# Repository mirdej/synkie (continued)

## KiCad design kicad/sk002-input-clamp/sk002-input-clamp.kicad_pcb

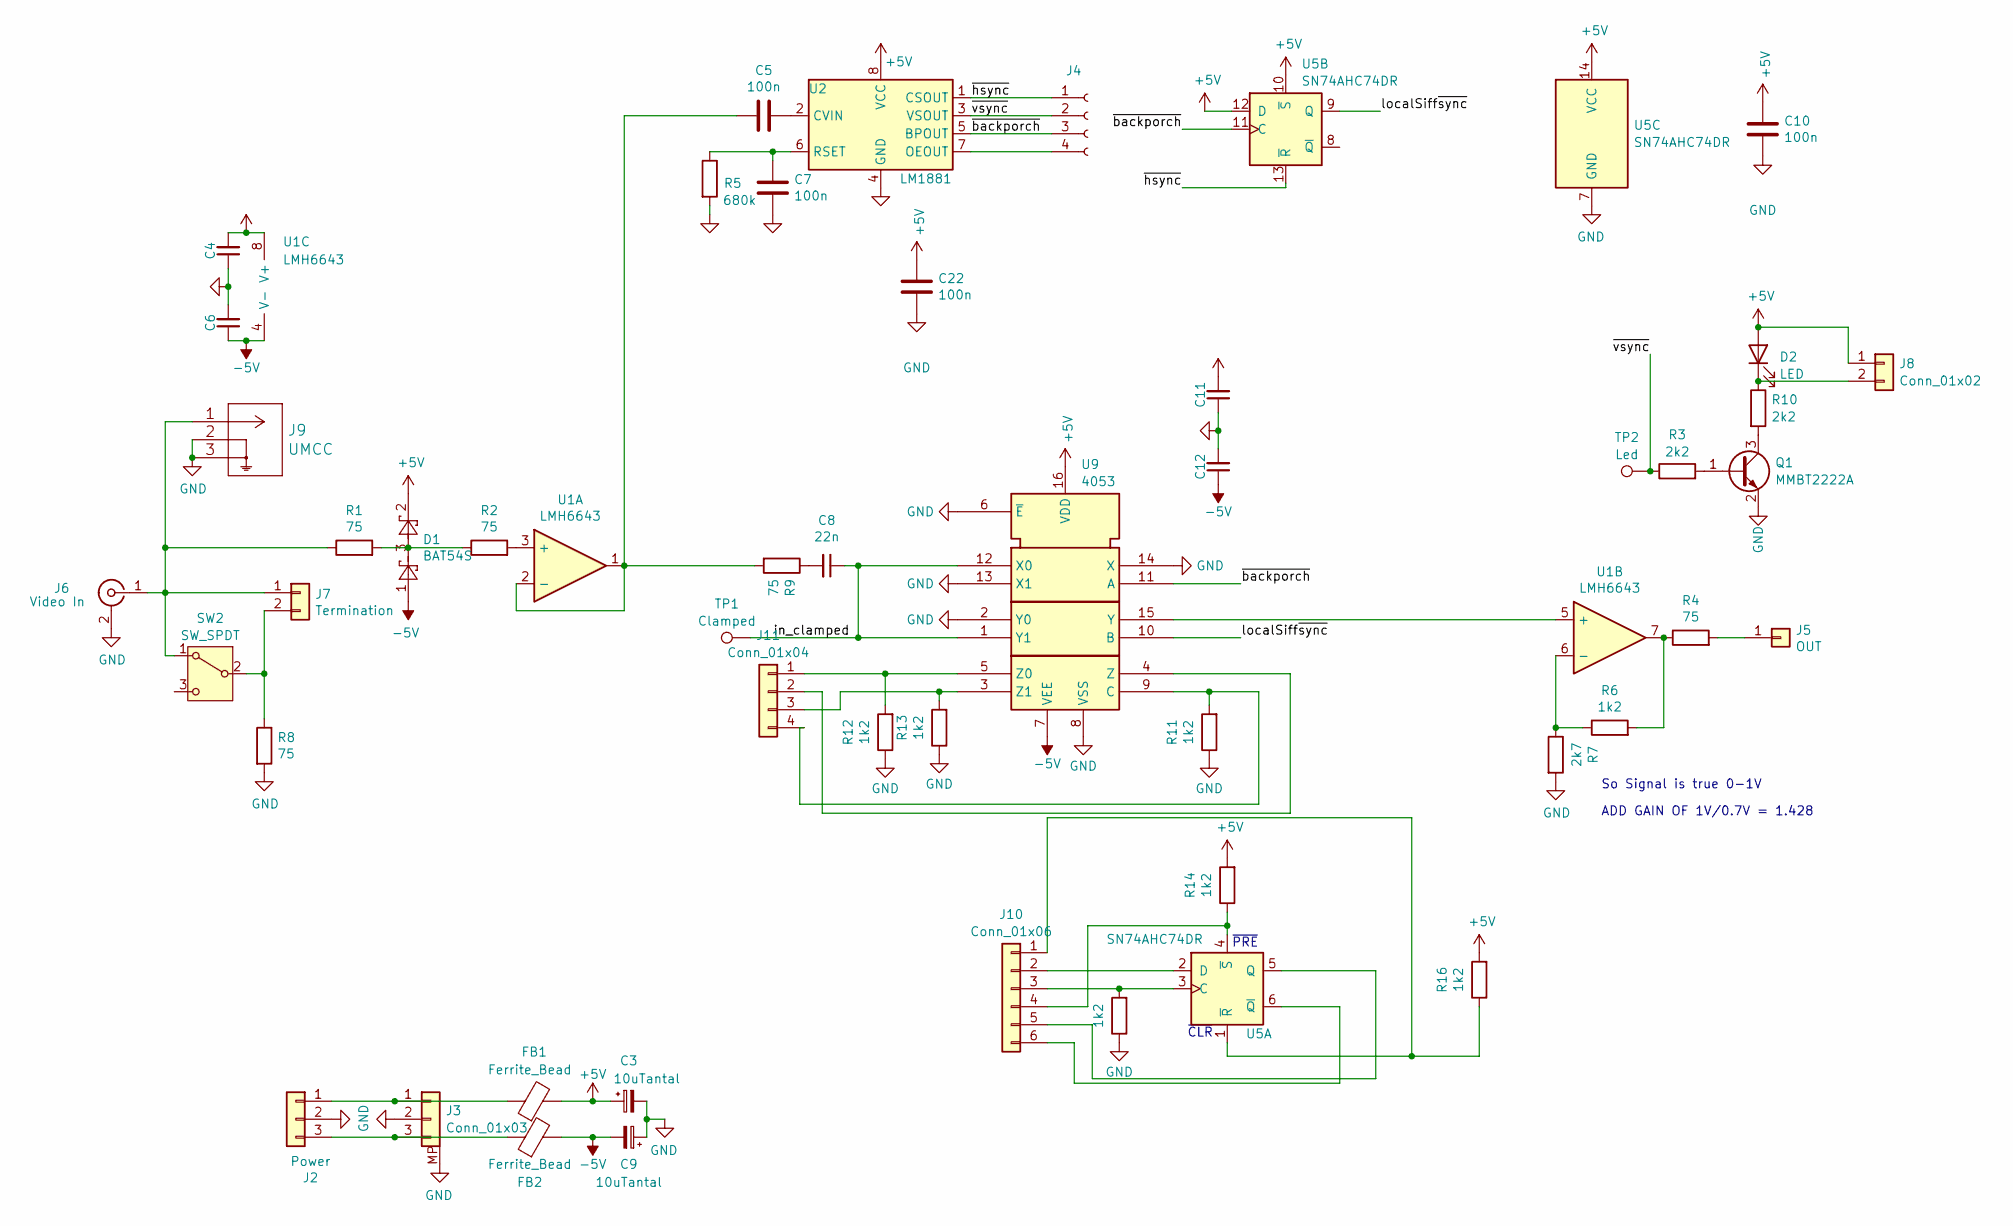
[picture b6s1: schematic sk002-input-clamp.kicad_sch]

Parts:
C3, C9: 10uTantal; CP_EIA-3216-18_Kemet-A; LCSC C7171
C4, C5, C6, C7, C10, C11, C12, C22: 100n; C_0603_1608Metric; LCSC C14663
C8: 22n; C_0603_1608Metric; LCSC C21122
D1: BAT54S; SOT-23; LCSC C7420333
D2: LED; LED_0805_2012Metric; LCSC C2296
FB1, FB2: Ferrite_Bead; L_0805_2012Metric; LCSC C1017
J2: Power; Molex_KK-254_AE-6410-03A_1x03_P2.54mm_Vertical
J3: Conn_01x03; Hirose_DF13-03P-1.25DSA_1x03_P1.25mm_Vertical; LCSC C293633
J4: Conn_01x04_Socket; PinHeader_1x04_P2.54mm_Vertical
J5: OUT; TestPoint_THTPad_D4.0mm_Drill2.0mm
J6: Video In; BNC_Aliexpress
J7: Termination; PinHeader_1x02_P2.54mm_Vertical
J8: Conn_01x02; PinHeader_1x02_P2.54mm_Vertical
J9: UMCC; TE_UMCC_2337019-1; LCSC C5137195
J10: Conn_01x06; PinHeader_1x06_P2.54mm_Vertical
J11: Conn_01x04; PinHeader_1x04_P2.54mm_Vertical
Q1: MMBT2222A; SOT-23; LCSC C8512
R1, R2, R4, R8, R9: 75; R_0603_1608Metric; LCSC C4275
R3, R10: 2k2; R_0603_1608Metric; LCSC C4190
R5: 680k; R_0603_1608Metric; LCSC C25822
R6, R11, R12, R13, R14, R15, R16: 1k2; R_0603_1608Metric; LCSC C22765
R7: 2k7; R_0603_1608Metric; LCSC C13167
SW2: SW_SPDT; CUS-12TB_NDC; LCSC C109335
TP1: Clamped; TestPoint_Pad_2.0x2.0mm
TP2: Led; TestPoint_Pad_D1.0mm
U1: LMH6643; VSSOP-8_3x3mm_P0.65mm; LCSC C478382
U2: LM1881; SOIC-8_3.9x4.9mm_P1.27mm; LCSC C518922
U5: SN74AHC74DR; SOIC-14_3.9x8.7mm_P1.27mm; LCSC C7621
U9: 4053; SOIC-16_3.9x9.9mm_P1.27mm; LCSC C7500846

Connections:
+5V: C3.1, C4.2, C10.1, C11.2, C22.1, D1.2, D2.2 (A), FB1.2, J8.1, R14.2, R16.2, U1.8 (V+), U2.8 (VCC), U5.10 (~S), U5.12 (D), U5.14 (VCC), U9.16 (VDD)
-5V: C6.1, C9.2, C12.1, D1.1, FB2.2, U1.4 (V-), U9.7 (VEE)
/in_clamped: C8.1, TP1.1 (1_1), U9.1 (Y1), U9.12 (X0)
/localSiff~sync: U5.9 (Q), U9.10 (B)
/~backporch: J4.3, U2.5 (BPOUT), U5.11 (C), U9.11 (A)
/~hsync: J4.1, U2.1 (CSOUT), U5.13 (~R)
/~vsync: J4.2, R3.1, TP2.1 (1_1), U2.3 (VSOUT)
GND: C3.2, C4.1, C6.2, C7.2, C9.1, C10.2, C11.1, C12.2, C22.2, J2.2, J3.2, J3.MP, J6.2 (Ext), J9.2, J9.3, Q1.2 (E), R5.2, R7.2, R8.2, R11.1, R12.1, R13.1, R15.1, U2.4 (GND), U5.7 (GND), U9.2 (Y0), U9.6 (~E), U9.8 (VSS), U9.13 (X1), U9.14 (X)
unnamed: C8.2, R9.1
unnamed: D1.3, R1.2, R2.1
unnamed: D2.1 (K), J8.2, R10.1
unnamed: FB1.1, J2.1, J3.1
unnamed: FB2.1, J2.3, J3.3
unnamed: J4.4, U2.7 (OEOUT)
unnamed: J5.1 (Pin_1_1), R4.2
unnamed: J6.1 (In), J7.1, J9.1, R1.1, SW2.1 (A)
unnamed: J7.2, R8.1, SW2.2 (B)
unnamed: J10.1, R16.1, U5.1 (~R)
unnamed: J10.2, U5.2 (D)
unnamed: J10.3, R15.2, U5.3 (C)
unnamed: J10.4, R14.1, U5.4 (~S)
unnamed: J10.5, U5.5 (Q)
unnamed: J10.6, U5.6 (~Q)
unnamed: J11.1, R12.2, U9.5 (Z0)
unnamed: J11.2, U9.4 (Z)
unnamed: J11.3, R13.2, U9.3 (Z1)
unnamed: J11.4, R11.2, U9.9 (C)
unnamed: Q1.1 (B), R3.2
unnamed: Q1.3 (C), R10.2
unnamed: R4.1, R6.2, U1.7
unnamed: R2.2, U1.3 (+)
unnamed: C5.2, R9.2, U1.1, U1.2 (-)
unnamed: U1.5 (+), U9.15 (Y)
unnamed: R6.1, R7.1, U1.6 (-)
unnamed: C5.1, U2.2 (CVIN)
unnamed: C7.1, R5.1, U2.6 (RSET)

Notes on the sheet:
~{CLR}
ADD GAIN OF 1V/0.7V = 1.428
~{PRE}
So Signal is true 0-1V

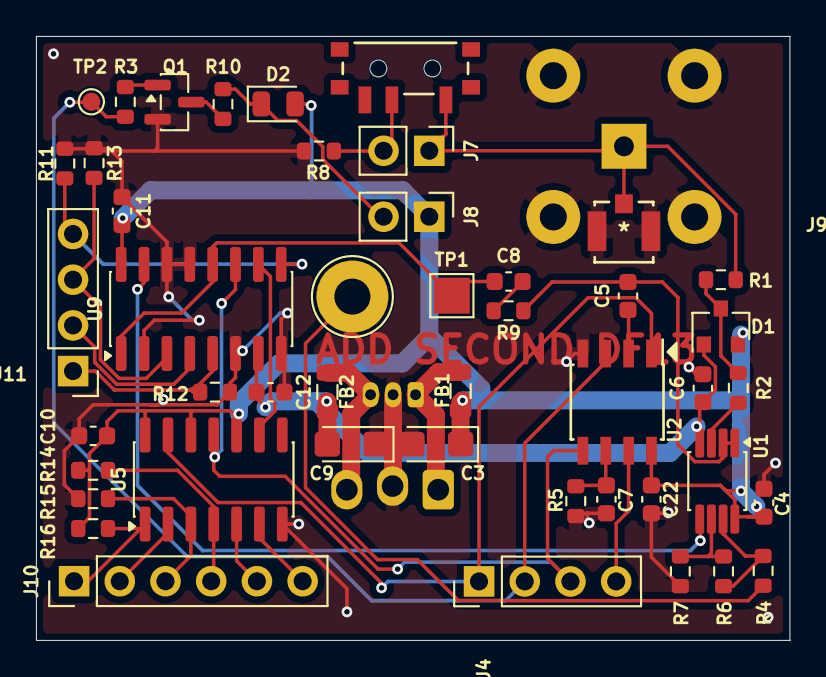
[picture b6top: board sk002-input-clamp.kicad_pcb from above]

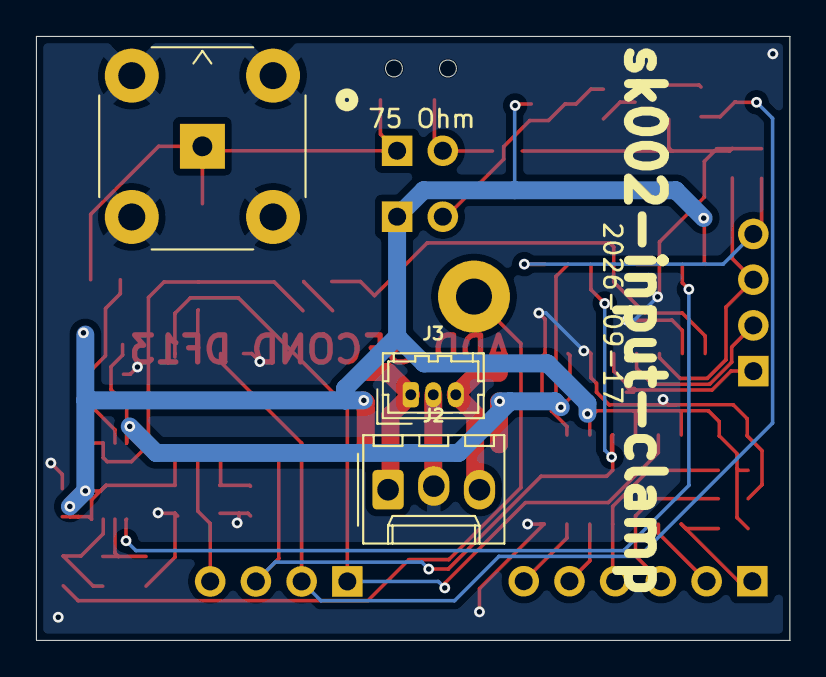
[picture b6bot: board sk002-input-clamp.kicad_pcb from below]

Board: 2 copper layers, 41.9 x 33.6 mm, 49 parts (3 on the bottom side), 36 nets.

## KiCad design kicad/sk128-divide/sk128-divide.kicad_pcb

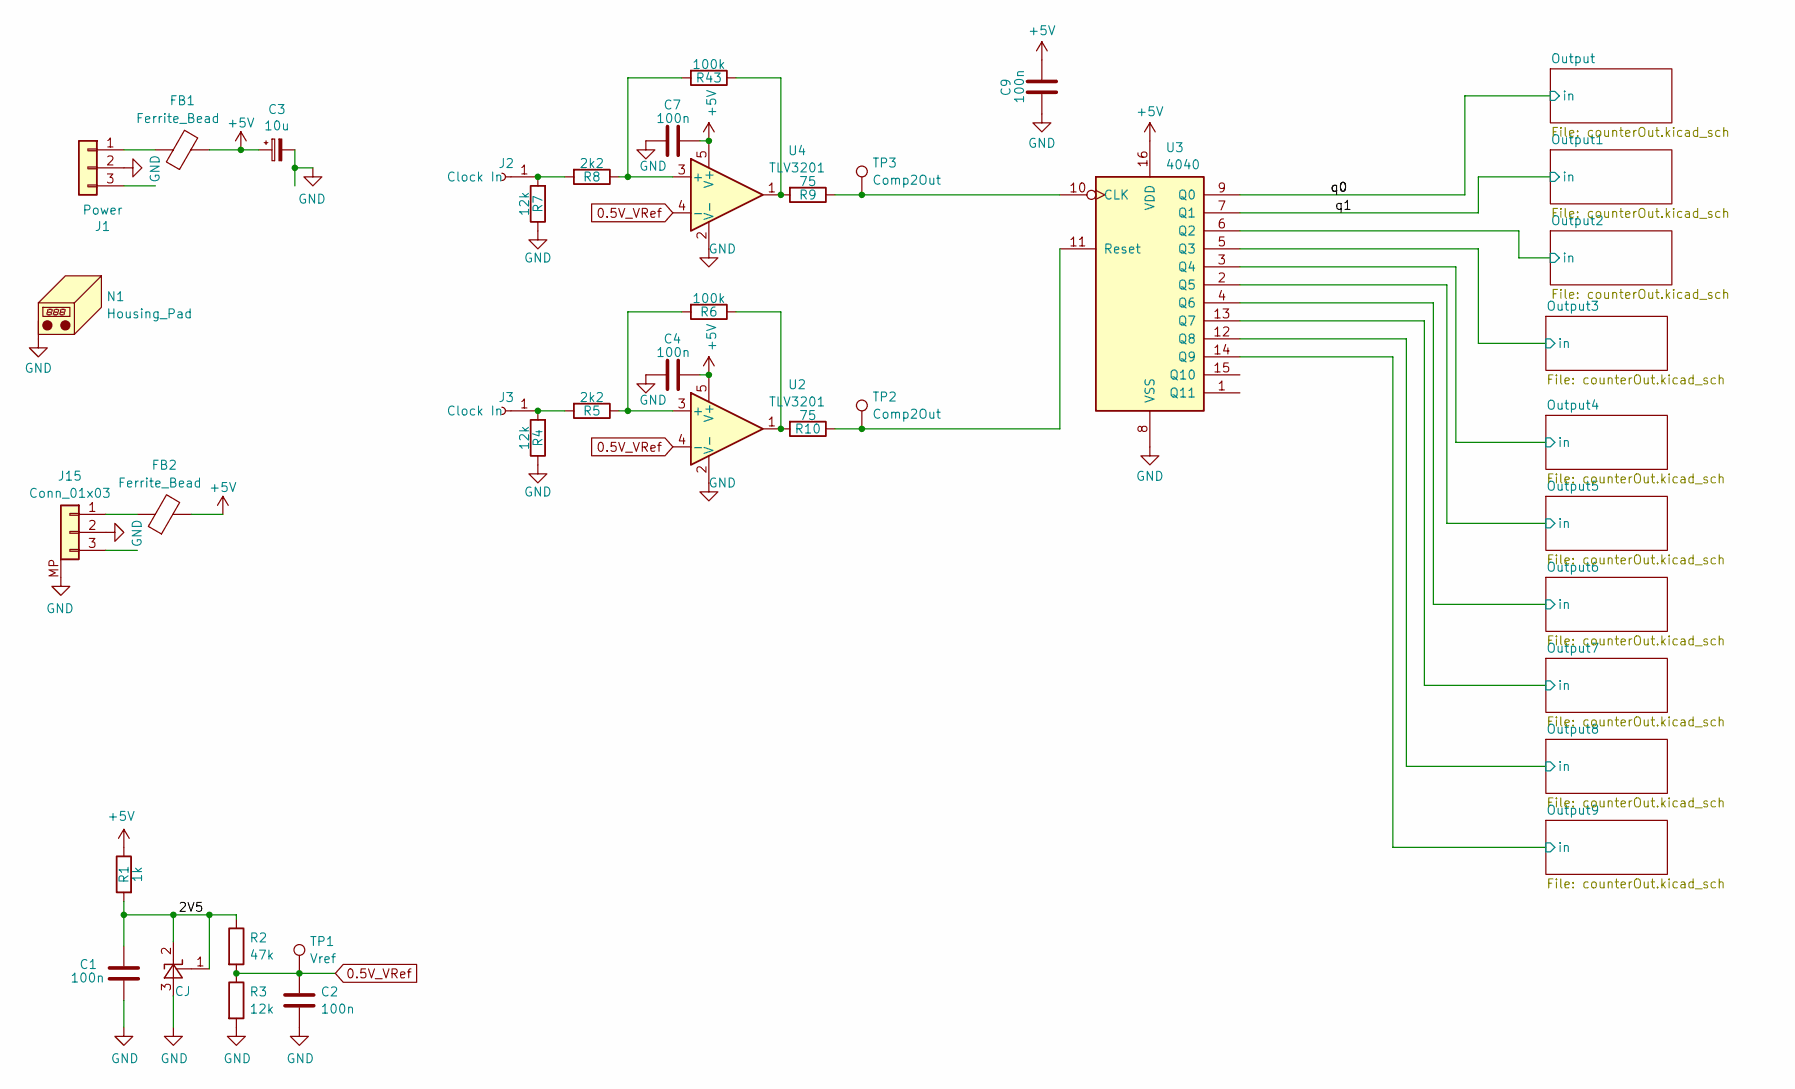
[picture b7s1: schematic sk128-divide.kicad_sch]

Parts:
C1, C2, C4, C7, C9: 100n; C_0603_1608Metric; LCSC C14663
C3: 10u; C_0805_2012Metric; LCSC C15850
FB1, FB2: Ferrite_Bead; L_0805_2012Metric; LCSC C1017
J1: Power; Molex_KK-254_AE-6410-03A_1x03_P2.54mm_Vertical_SMD
J2, J3: Clock In; Banana2mm-Löthülse
J15: Conn_01x03; Molex_PicoBlade_53398-0371_1x03-1MP_P1.25mm_Vertical; LCSC C293633
N1: Housing_Pad; Frontplate_20mm
R1: 1k; R_0603_1608Metric; LCSC C21190
R2: 47k; R_0603_1608Metric; LCSC C25819
R3, R4, R7: 12k; R_0603_1608Metric; LCSC C22790
R5, R8: 2k2; R_0603_1608Metric; LCSC C4190
R6, R43: 100k; R_0603_1608Metric; LCSC C25803
R9, R10: 75; R_0603_1608Metric; LCSC C4275
TP1: Vref; TestPoint_Pad_D1.0mm
TP2, TP3: Comp2Out; TestPoint_Pad_D1.0mm
U1: CJ; SOT-23; LCSC C3113
U2, U4: TLV3201; SOT-23-5; LCSC C105188
U3: 4040; SOIC-16_3.9x9.9mm_P1.27mm; LCSC C22390247

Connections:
0.5V_VRef: C2.1, R2.2, R3.1, TP1.1 (1_1), U2.4 (-), U4.4 (-)
+5V: C3.1, C4.2, C7.2, C9.2, FB1.2, FB2.2, R1.1, U2.5 (V+), U3.16 (VDD), U4.5 (V+); also elsewhere on the board
/2V5: C1.1, R1.2, R2.1, U1.1 (R), U1.2 (K)
/Output2/in: U3.6 (Q2); also elsewhere on the board
/Output3/in: U3.5 (Q3); also elsewhere on the board
/Output4/in: U3.3 (Q4); also elsewhere on the board
/Output5/in: U3.2 (Q5); also elsewhere on the board
/Output6/in: U3.4 (Q6); also elsewhere on the board
/Output7/in: U3.13 (Q7); also elsewhere on the board
/Output8/in: U3.12 (Q8); also elsewhere on the board
/Output9/in: U3.14 (Q9); also elsewhere on the board
/Output/in: U3.9 (Q0); also elsewhere on the board
/q1: U3.7 (Q1); also elsewhere on the board
GND: C1.2, C2.2, C3.2, C4.1, C7.1, C9.1, J1.2, J15.2, J15.MP, N1.1 (PAD_1), R3.2, R4.1, R7.1, U1.3 (A), U2.2 (V-), U3.8 (VSS), U4.2 (V-); also elsewhere on the board
unnamed: FB1.1, J1.1
unnamed: J2.1 (Pin_1_1), R7.2, R8.2
unnamed: J3.1 (Pin_1_1), R4.2, R5.2
unnamed: FB2.1, J15.1
unnamed: R6.1, R10.2, U2.1
unnamed: R9.2, R43.1, U4.1
unnamed: R5.1, R6.2, U2.3 (+)
unnamed: R9.1, TP3.1 (1_1), U3.10 (CLK)
unnamed: R10.1, TP2.1 (1_1), U3.11 (Reset)
unnamed: R8.1, R43.2, U4.3 (+)

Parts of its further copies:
R18: 2k2; R_0603_1608Metric; LCSC C4190

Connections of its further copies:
unnamed 15: R18.1; also elsewhere on the board
unnamed 41: R18.2; also elsewhere on the board

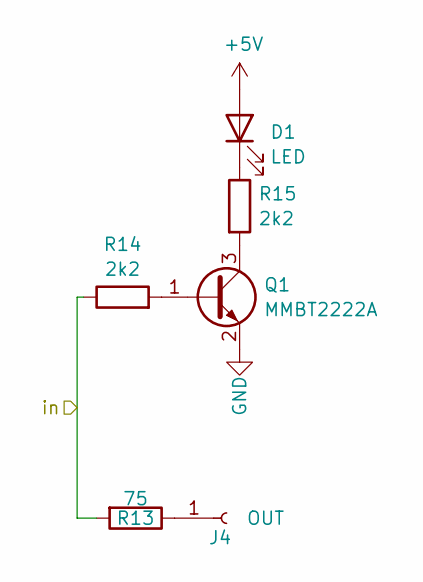
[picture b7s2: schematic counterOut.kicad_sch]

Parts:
D1: LED; LED_1206_3216Metric_ReverseMount_Hole1.8x2.4mm; LCSC C125108
J4: OUT; Banana2mm-Löthülse
Q1: MMBT2222A; SOT-23; LCSC C8512
R13: 75; R_0603_1608Metric; LCSC C4275
R14, R15: 2k2; R_0603_1608Metric; LCSC C4190

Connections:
+5V: D1.2 (A); also elsewhere on the board
/Output/in: R13.2, R14.1; also elsewhere on the board
GND: Q1.2 (E); also elsewhere on the board
unnamed: D1.1 (K), R15.1
unnamed: J4.1 (Pin_1_1), R13.1
unnamed: Q1.1 (B), R14.2
unnamed: Q1.3 (C), R15.2

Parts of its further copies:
D2, D3, D4, D5, D6, D7, D8, D9, D10: LED; LED_1206_3216Metric_ReverseMount_Hole1.8x2.4mm; LCSC C125108
J5, J6, J7, J8, J9, J10, J11, J12, J13: OUT; Banana2mm-Löthülse
Q2, Q3, Q4, Q5, Q6, Q7, Q8, Q9, Q10: MMBT2222A; SOT-23; LCSC C8512
R16, R18, R19, R21, R22, R24, R25, R27, R28, R30, R31, R33, R34, R36, R37, R39, R40, R42: 2k2; R_0603_1608Metric; LCSC C4190
R17, R20, R23, R26, R29, R32, R35, R38, R41: 75; R_0603_1608Metric; LCSC C4275

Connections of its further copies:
+5V: D2.2 (A), D3.2 (A), D4.2 (A), D5.2 (A), D6.2 (A), D7.2 (A), D8.2 (A), D9.2 (A), D10.2 (A); also elsewhere on the board
/Output2/in: R22.1, R23.2; also elsewhere on the board
/Output3/in: R19.1, R20.2; also elsewhere on the board
/Output4/in: R25.1, R26.2; also elsewhere on the board
/Output5/in: R28.1, R29.2; also elsewhere on the board
/Output6/in: R31.1, R32.2; also elsewhere on the board
/Output7/in: R34.1, R35.2; also elsewhere on the board
/Output8/in: R37.1, R38.2; also elsewhere on the board
/Output9/in: R40.1, R41.2; also elsewhere on the board
/q1: R16.1, R17.2; also elsewhere on the board
GND: Q2.2 (E), Q3.2 (E), Q4.2 (E), Q5.2 (E), Q6.2 (E), Q7.2 (E), Q8.2 (E), Q9.2 (E), Q10.2 (E); also elsewhere on the board
unnamed: D2.1 (K), R18.1
unnamed: D3.1 (K), R21.1
unnamed: D4.1 (K), R24.1
unnamed: D5.1 (K), R27.1
unnamed: D6.1 (K), R30.1
unnamed: D7.1 (K), R33.1
unnamed: D8.1 (K), R36.1
unnamed: D9.1 (K), R39.1
unnamed: D10.1 (K), R42.1
unnamed: J5.1 (Pin_1_1), R17.1
unnamed: J6.1 (Pin_1_1), R20.1
unnamed: J7.1 (Pin_1_1), R23.1
unnamed: J8.1 (Pin_1_1), R26.1
unnamed: J9.1 (Pin_1_1), R29.1
unnamed: J10.1 (Pin_1_1), R32.1
unnamed: J11.1 (Pin_1_1), R35.1
unnamed: J12.1 (Pin_1_1), R38.1
unnamed: J13.1 (Pin_1_1), R41.1
unnamed: Q2.1 (B), R16.2
unnamed: Q2.3 (C), R18.2
unnamed: Q3.1 (B), R19.2
unnamed: Q3.3 (C), R21.2
unnamed: Q4.1 (B), R22.2
unnamed: Q4.3 (C), R24.2
unnamed: Q5.1 (B), R25.2
unnamed: Q5.3 (C), R27.2
unnamed: Q6.1 (B), R28.2
unnamed: Q6.3 (C), R30.2
unnamed: Q7.1 (B), R31.2
unnamed: Q7.3 (C), R33.2
unnamed: Q8.1 (B), R34.2
unnamed: Q8.3 (C), R36.2
unnamed: Q9.1 (B), R37.2
unnamed: Q9.3 (C), R39.2
unnamed: Q10.1 (B), R40.2
unnamed: Q10.3 (C), R42.2

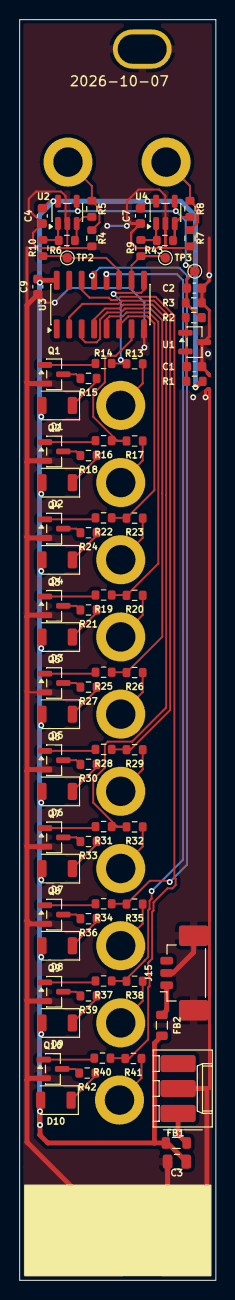
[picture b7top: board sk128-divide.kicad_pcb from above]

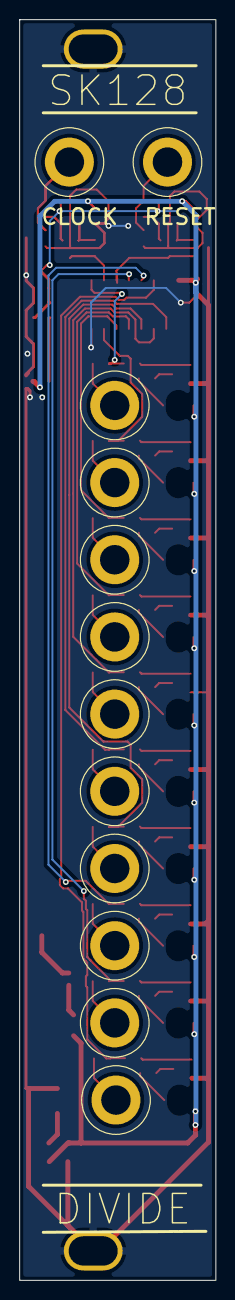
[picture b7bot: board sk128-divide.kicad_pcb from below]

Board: 2 copper layers, 20.0 x 128.5 mm, 91 parts (13 on the bottom side), 64 nets.

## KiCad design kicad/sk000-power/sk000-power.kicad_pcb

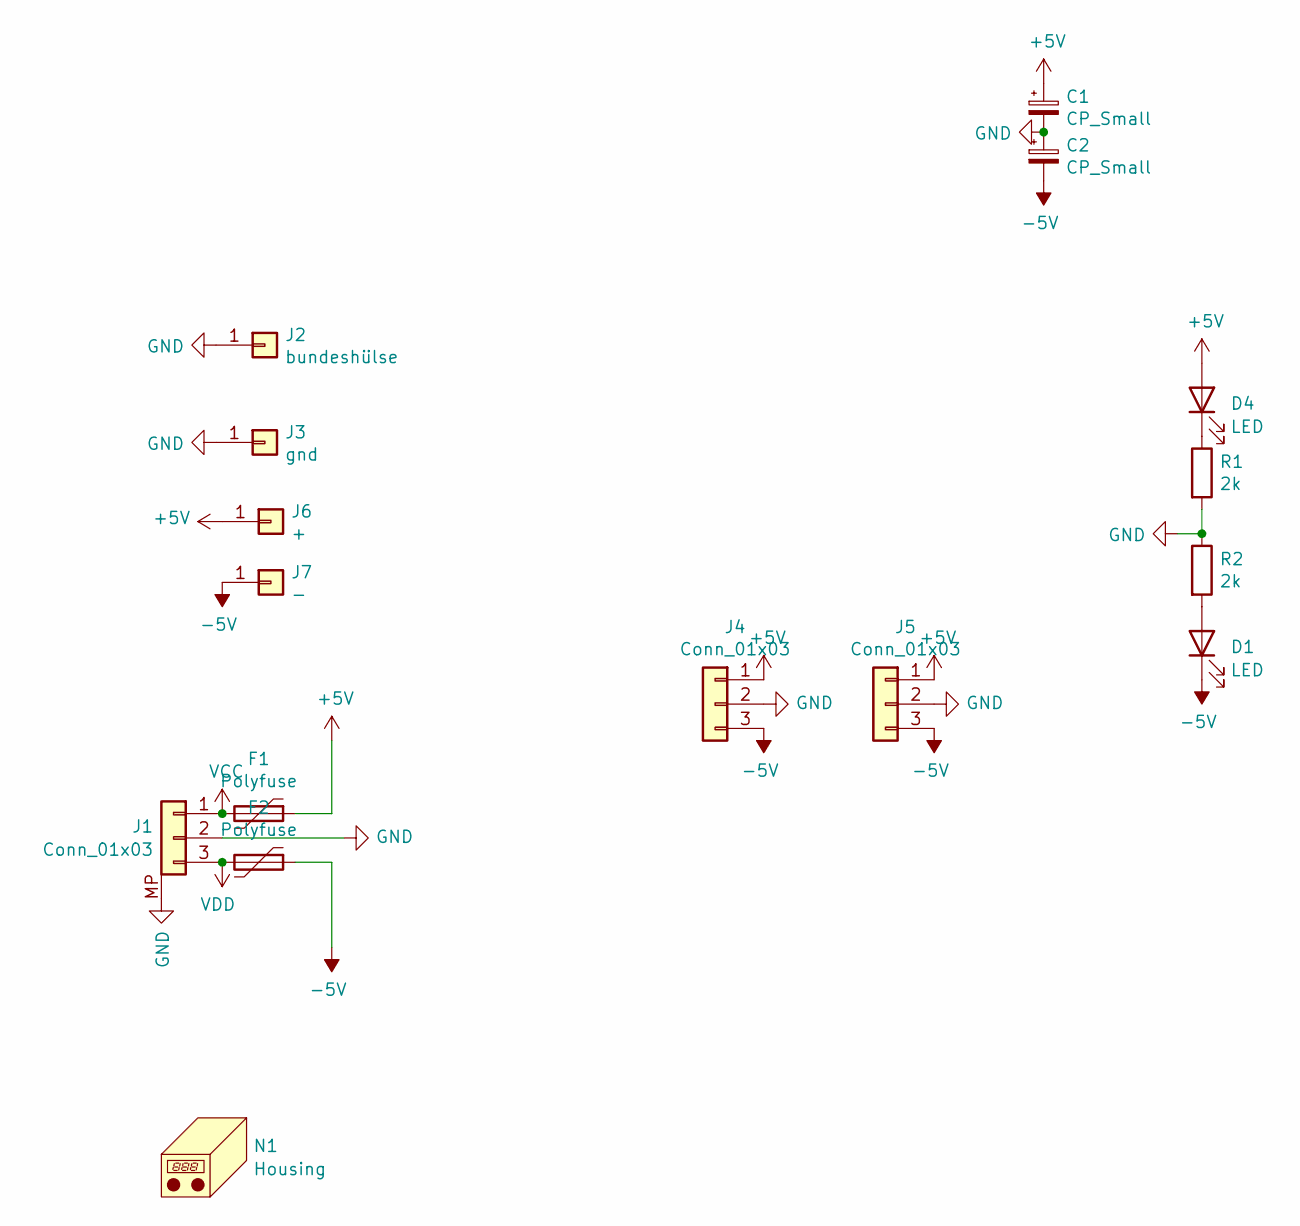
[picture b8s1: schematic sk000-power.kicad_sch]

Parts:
C1, C2: CP_Small; C_1206_3216Metric_Pad1.42x1.75mm_HandSolder; LCSC C13585
D1, D4: LED; LED_1206_3216Metric_ReverseMount_Hole1.8x2.4mm; LCSC C125108
F1, F2: Polyfuse; L_1206_3216Metric_Pad1.42x1.75mm_HandSolder; LCSC C22378342
J1: Conn_01x03; Molex_PicoBlade_53398-0371_1x03-1MP_P1.25mm_Vertical; LCSC C293633
J2: bundeshülse
J3: gnd; Banana2mm-Löthülse
J4: Conn_01x03; Molex_KK-254_AE-6410-03A_1x03_P2.54mm_Vertical
J5: Conn_01x03; Hirose_DF13-03P-1.25DSA_1x03_P1.25mm_Vertical
J6: +; Banana2mm-Löthülse
J7: -; Banana2mm-Löthülse
N1: Housing; Frontplate_10mm
R1, R2: 2k; R_0805_2012Metric_Pad1.15x1.40mm_HandSolder; LCSC C17604

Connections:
+5V: C1.1, D4.2 (A), F1.1, J4.1, J5.1, J6.1 (Pin_1_1)
-5V: C2.2, D1.1 (K), F2.1, J4.3, J5.3, J7.1 (Pin_1_1)
GND: C1.2, C2.1, J1.2, J1.MP, J2.1 (Pin_1_1), J3.1 (Pin_1_1), J4.2, J5.2, R1.2, R2.1
unnamed: D1.2 (A), R2.2
unnamed: D4.1 (K), R1.1
VCC: F1.2, J1.1
VDD: F2.2, J1.3

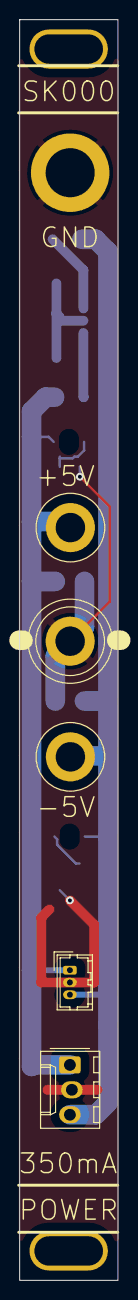
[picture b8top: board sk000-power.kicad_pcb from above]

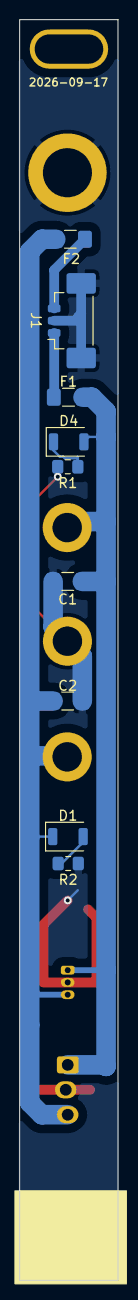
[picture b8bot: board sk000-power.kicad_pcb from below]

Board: 2 copper layers, 10.0 x 128.5 mm, 16 parts (9 on the bottom side), 7 nets.

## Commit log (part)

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2013-11-23 another take on the master time module
2013-11-23 now with audio click track support.
2013-11-23 audio input board with envelope replaces ac coupling and biasing on sk556-time board
2013-11-23 supply of ramp out opamp was wrong way round
2013-11-23 first version of cv-looped-motor control
2013-11-23 half-hearted attempt to make this stuff synchronisable by beat interrupt. will move to ramp synchronized approach
2013-11-24 one channel woring
2013-11-26 main.c appartently got corrupted by bad copy-paste jobs for other modules. reverted back to revision 104
2013-12-09 added second version of ramps module
2013-12-10 corrected r and c values
2013-12-29 improved gain by ting R215 to base of bias pot. reduced oscillation with bigger r307/r308
2013-12-29 added first version of sk800
2013-12-30 second version of subcarrier module. untested
2014-05-26 added sk010-refgen
2014-05-26 added board
2014-05-28 added firmware
2014-05-28 re-wrote firmware in assembler
2014-05-29 added generation of sync bus signals*
2014-05-31 second prototype and follow-up corrections
2014-08-08 added smoothing
2014-10-13 added very old audio-cv module from 2012
2014-10-13 added newly routed aux in module using triple digit naming scheme
2014-10-13 adapted disasm target for using build folder
2014-10-13 better board layout
2014-10-14 added offset pot, routed board
2014-10-14 added frontplate
2014-10-14 added note about pot pad sizes
2014-10-14 added sk590-audio-inject
2014-12-29 added missing connection and capacitor, finished routing
2014-12-30 reimplemented audio click detection
2015-05-24 added subcarrier oscillator study
2015-05-24 updated values, small fixes
2016-01-03 Migrating wiki contents from Google Code
2016-01-04 corrected date on pcb
2016-01-05 changed footprint of transfo, added 100p anti-oscillation capas
2016-01-06 fixed power supply connector was reversed
2016-01-08 added .gitignore
2016-01-08 added second version of subcarrier proto, and synkie eagle lib
2016-01-08 added comment about values on paper schema
2016-02-06 moved sync connector ôut of way of banana plug
2016-05-07 added mcugen
2016-05-07 removed lock files
2017-05-29 added rackmaster
2017-06-06 add vga breakout and multiple
2017-06-06 clean up silk layers for production
2017-08-04 only listen to every other color burst because of alternating phase
2017-08-04 add new modules
2017-10-14 add sk242 chroma
2017-10-27 first version of untested firmware
2017-11-06 version1 of stepsequencer
2017-11-06 forgot file
2018-03-19 michis mods
2018-03-19 add spectrum analyzer
2018-03-19 add eqs
2018-03-19 add clipper
2018-03-20 added .lck files to gitignore
2018-03-20 sk181-clipper: replaced buffer op amps and diodes with transistors
2018-03-22 fixed(?) ramp input
2018-03-22 sk001: new clipper with transistors
2018-03-22 add phgaseshift
2018-03-23 scabi with logarithmic gain control
2018-03-23 named signals
2018-03-23 add 4x4 matrix mixer
2018-03-24 scabi-log scale: sum before exponentiating
2018-05-01 less capacity on output. no resistor
2018-05-02 added videobuffer
2018-05-03 sorted out pot order
2018-05-11 increased matrix mixer feedback resistances to avoid ringing
2018-09-09 rackmaster: added lowpass to lm1881 input
2018-09-09 mcugen: added pull-downs for outputs, switched supply pins on programming connector
2018-10-06 routed remaining air wire
2018-10-10 correct date
2018-10-22 add frontplate
2018-10-30 correct resistor values)
2018-11-02 first levelmeter
2019-05-28 add new kicad modules
2019-06-02 added allpass and bwlim experiments
2019-11-11 various
2019-11-12 ported sk108-scabi-log to kicad
2019-11-12 addedd kicad template for synkie modules
2019-11-12 modified BAT54S symbol to remove weird pin standing out
2019-11-12 added default power and signal in sections to synkie module template
2019-11-12 added some kicad temporary files to .gitignore
2019-11-12 changed PEMX1 symbol to have pin names outside
2019-11-14 added sk161-modular-mixer; NOTE: board needs to be corrected to adapt to corrected slider pot footprint!
2019-11-14 added conn 1x10 to synkie_symbols
2019-11-14 fixed symbols / footprints references in sk034-allpass
2019-11-15 added footprint and maximum module board size to template
2019-11-15 added new modular mixer master board
2019-11-15 updated values for better image
2019-11-15 minimized some bare zones
2019-11-15 change footfrints
2019-11-15 corrected footprint of ferrite beads
2019-11-15 added modular mixer channel board
2019-11-15 new values
2019-11-15 added obsolescence note for old 'sk161-modular-mixer.pro' project
2019-11-16 updated LT1228 symbol
2019-11-18 mixer modules ready for fabrication. allpass with dual-pot
2019-11-18 change to 2pin connectors for sync signal
2019-12-08 modular mixer: updated values for better gain ranges
2019-12-09 new scabi-log with transistors for U->I conversion
2020-08-13 modular mixer for fabrication
2020-08-18 added PMBT3906YS dual PNP symbol and footprint
2020-08-19 increased pad size of SOT-666 footprint for easier etching/soldering
2020-08-19 added diode symbol to library
2020-08-19 added new clipper with automatic levels
2020-08-19 add new sync splitter
2020-08-19 add new resyncer
2020-08-20 Better black level for clipper
2020-08-20 fixed symbols for PMBT3906 were referencing rescue library
2020-08-20 .gitignore
2020-08-20 added LM311 to synkie_symbols
2020-08-21 prepare microsynkie for fabrication
2020-08-21 updated synkie_symbols.bck
2020-08-21 add atmega88 symbol
2020-08-21 add dac
2020-08-25 smaller switch footprint
2020-08-27 add symbols
2020-08-27 add footprints
2020-08-27 add sk720 schematic
2020-08-28 ready for fab
2020-09-04 change footprints C to 0603
2020-09-14 add firmare. change 1206 footprints to 0805
2020-09-14 add laser files
2020-09-19 add sk730
2020-09-28 change globals to valatile to prevent crashes. make version for pragramming throuigh Arduino IDE
2020-10-15 added footprint of uwe pots to library
2020-10-16 added sk508-chua
2020-10-18 first version 4fach compa mit fix levels für die stufen 0-1V
2020-12-13 4 layer versions. scabi with levelmeter
2020-12-24 c footprints
2020-12-25 better color frequency response
2020-12-26 module template: changed default input resistor values
2020-12-26 added LM339 to synkie library
2020-12-26 added sk221-compa-edges
2021-01-03 power supply protection diodes
2021-01-06 add anyma logo
2021-01-13 write steps to eeprom
2021-01-14 wait 30secs before writing eeprom in order to limit number of succesive writes
2021-05-15 added gyrator-based equalizer experiment
2021-05-15 added footprint for big smd elcos to synkie_footprints
2021-05-15 added trigger regularizer
2021-05-15 increased trigreg output pulse length
2021-09-06 add filters from circuitcontrol drersden
2021-09-06 add sk light/cv modules
2021-09-13 note on moog
2021-09-24 new resyncer based on anymix21 output. simply named sk003-output from now on
2021-09-24 add genlock in module. this is the new sync-splitter
2021-09-24 rename with right prefix
2021-09-24 fix sheet link
2021-09-29 correct polarity
2021-10-02 correct pot polarity
2021-10-15 oscra changes
2021-10-15 update kicad libraries
2021-10-16 add new input clamp
2021-10-17 add handmade sk006-version
2021-10-23 add pal notice
2021-10-23 version with dual-trans and INA
2021-10-23 add new tourbox
2021-10-23 first version of subcarrier module
2021-10-24 add simplified version (not fully tested)
2021-10-31 add multiple
2021-10-31 add missing 75Ohm termination on input
2021-11-02 add missing jtag vzarget
2021-11-11 add documentation
2021-11-11 cosmetics
2021-11-14 delay does not work. will change to fpga
2021-11-23 add missing pulldown. change r1206 to 0805
2021-12-03 add vcos
2021-12-04 correct footprints. more gain on subcarrier
2021-12-21 add power distro
2021-12-21 burstphase
2021-12-21 add matrix
2021-12-21 rgb module
2021-12-21 add logo symbol
2021-12-21 sk108-scabi-log: fixed op amp inputs were reversed since 2020-12-13 (commit 16a4c41fa6f06a2b7dd2fa5efc88025a5135e06a)
2021-12-21 fixed a few typos in readme
2021-12-21 sk001-genlock-in: changed logo symbol to reference synkie_symbols
2021-12-21 added fp-lib-table and sym-lib-table to gitignore, fixed bom ignore
2021-12-21 added eagle-import files in eagle folder (generated by kicad) to gitignores
2021-12-22 missing capacitor
2021-12-27 change to sykiepad
2021-12-30 add umcc connector
2022-01-01 improve return paths in pcb. stacking order should be F,B,In2,In1
2022-01-20 change layer stackup
2023-01-18 add monitor resyncer
2023-01-31 add buffers for input and burst
2023-04-08 added sk509-noise
2024-08-26 sk502-vco-triple: removed bom
2024-08-26 sk509-noise: added comments on things to try on schema
2024-08-26 removed empty 0034-1496test
2024-08-26 update symbols
2024-08-27 add trigger guzzi
2024-08-27 updated sk509-noise for new experimental board; component values set so that circuit corresponds to previous prototype
2024-08-27 update to lateat state of prototype board
2024-08-27 updated schema to match final version; board needs re-routing!
2024-08-27 route for china
2024-08-27 add pulsedelay
2024-08-29 added sk504-ltvco
2024-08-29 added some more kicad-specific entries (*-backups/, *.kicad_prl) to .gitignores
2024-09-03 gitignore
2024-09-03 add frontplate part library
2024-09-03 add ne frontplate
2024-09-03 updated schema with values tuned for low-frequency vco; board outdate!
2024-09-03 migrate symbol library
2024-09-03 new kicad version. note on dc levels/genlock
2024-09-18 reroute pcb
2024-09-27 deleted autosave files
2024-09-27 delet autosave
2024-09-27 sk800: removed question marks from resistor values
2025-10-16 add handmade anaguzzi
2025-10-21 added sk162-herd-mixer
2025-10-21 removed lib-table files from .gitignores
2025-10-21 sk162: removed unnecessary pull-down on inputs, reannotated
2025-10-21 added kicad _autosave-* files to gitignores
2025-10-25 update footprints
2025-10-25 added sk162-herd-mixer single-board version schema
2025-10-25 silkscreen
2025-10-25 add inverter
2025-10-25 remove prod folder
2025-10-25 added 'production' folder to gitignore
2025-10-25 partially routed sk162
2025-10-26 more 3d models
2025-10-26 routed sk162
2025-10-27 add some vias on suply
2025-10-28 added switch SPDT to synkie_symbols
2025-10-29 added sk110-cvadd
2025-10-30 sk162: corrected value of output gain resistor
2025-10-30 sk110: fixed bias pot low connection, fixed oscillation on bias op-amp
2025-10-30 added 4053, mounting hole to synkie_symbols
2025-10-30 corrected pin name on 4053 symbol
2025-10-30 added kicad .bak files to gitignores
2025-11-01 added MC1496 to synkie_symbols
2025-11-02 routed sk110-cvadd
2025-11-23 add crocodile pad
2025-11-24 sk162: updated schema according to first prototype: adapted output gain to 470/220, fixed termination of unused CFAs
2025-11-24 updated pcb for schema fixes
2025-11-24 added croco hole
2025-11-25 add sk801
2025-11-25 sk110: added croco hole, fixed: cfa termination, power connector orientation
2026-02-17 footprints
2026-02-17 new audio2cv, not routed yet
2026-02-18 layout
2026-02-19 add lfo
2026-02-19 add AI frequency propositions
2026-02-20 v9 schematic
2026-02-20 add new renamed sk001 with better subcarrier
2026-02-20 remove old sk001
2026-02-20 input buffert
2026-02-20 ac couple sc
2026-03-18 corrections
2026-03-23 new modules
2026-03-23 more changes
2026-03-23 more
2026-03-23 jlc version
2026-03-23 add ramps
2026-03-23 new bus, frontplates
2026-03-26 add module
2026-03-26 fix pot direction, schottkys
2026-03-26 more footprints
2026-03-26 new module
2026-03-26 fix poti direction, supply
2026-03-27 new output
2026-03-27 jlc order
2026-03-29 dd module
2026-03-29 production
2026-04-02 fix silkscreen, polarity
2026-04-14 fix outputs, silk
2026-04-15 fix r values
2026-05-13 fix output resistors, footprints, add picoblade
2026-05-15 cleanup
2026-05-15 add sk128
2026-05-15 remove old templates, add buiöding blocks
2026-05-15 add building blocks
2026-05-15 verticals, more designblocks
2026-05-15 ne5532 version
2026-05-15 add pms,pmm
2026-05-16 footprints and designblocks
2026-05-16 cleanup before redesign
2026-05-16 simpler version, new bus
2026-05-17 rgb module ad724 w hard clippers
2026-05-17 cheap clip?
2026-05-17 change big bus to 16 pins
2026-05-17 new version
2026-05-17 new bus connector
2026-06-01 buffered output 1V, 0.1V Hysteresis
